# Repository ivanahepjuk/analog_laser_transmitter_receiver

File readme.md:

Laser transmitter and receiver, version 2.0

!!! Please consider, that using the laser beam is dangerus and wearing protective tools is required !!!

This schematics and PCB was designed and created by me and I am ok with using this resources for your own educational purposes.
If you decide to build it and use it in public, you can use my credentials as a resource, of course,)

Created August 2016 ivanahepjuk@gmail.com

DATA:

There are project folders created by PCB tool Kicad 4.0.4, but I dont think it will work once you download it and open in Kicad 
(because Kicad has terrible library management). Therefore I created another folder with pdf document with schematics, 
pcb boards and I also included the .svg file in case you want to manually tune the boards a bit using for example inscape.
Enjoy

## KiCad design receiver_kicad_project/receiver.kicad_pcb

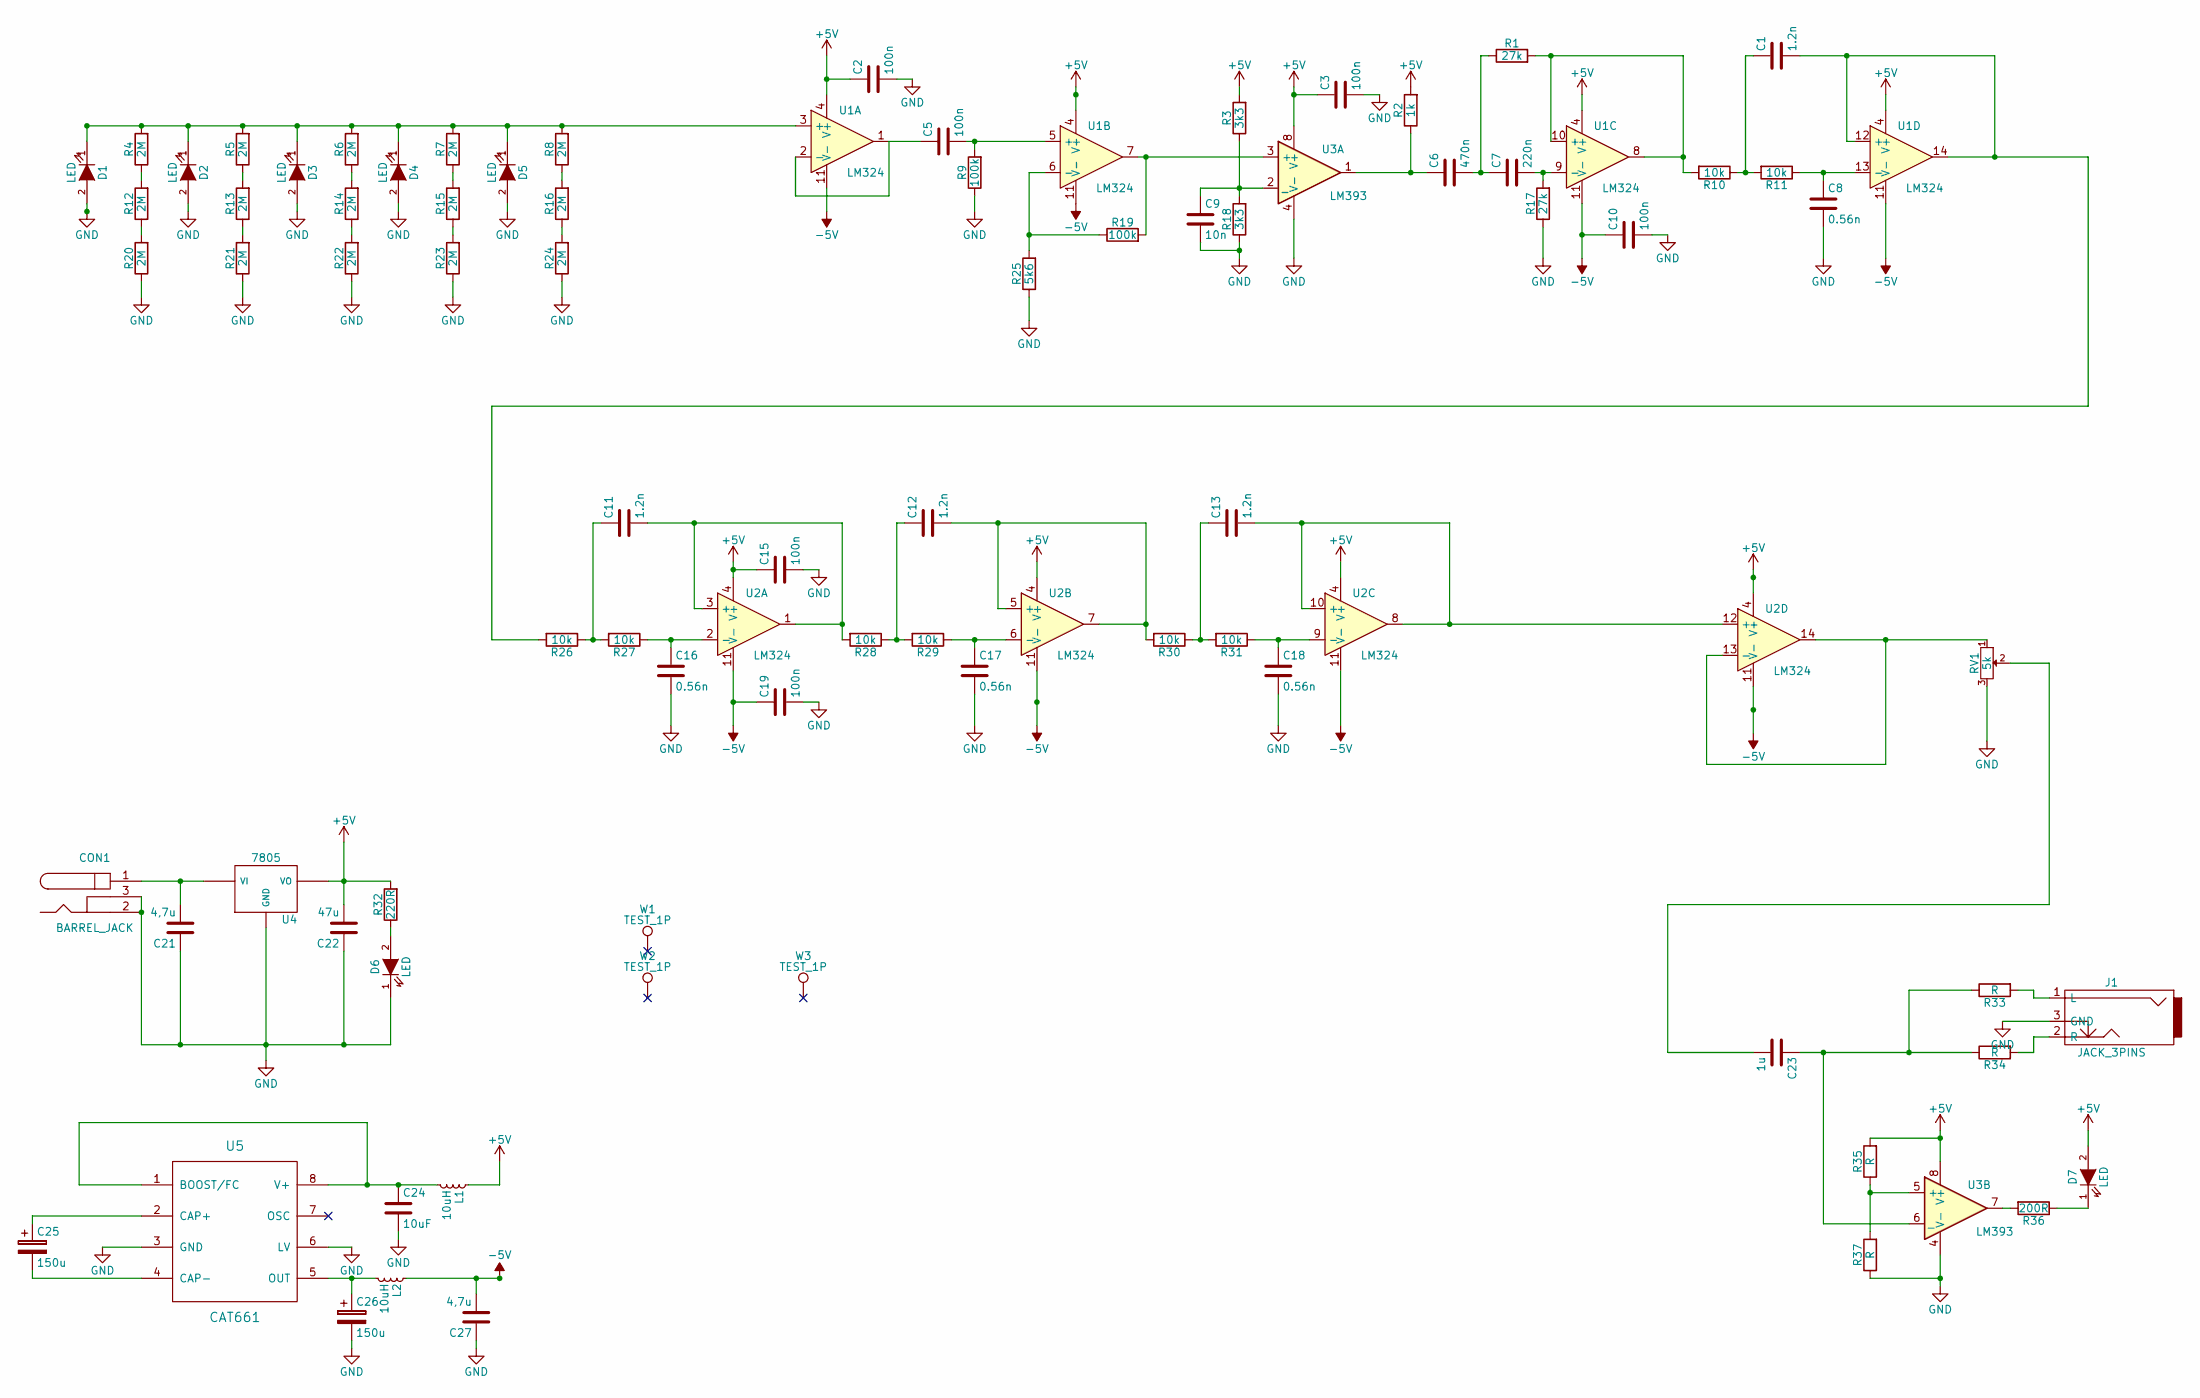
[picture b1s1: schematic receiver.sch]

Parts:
C1, C11, C12, C13: 1.2n; C_Disc_D3_P2.5
C2, C3, C5, C10, C15, C19: 100n; C_Disc_D3_P2.5
C6: 470n; C_Disc_D3_P2.5
C7: 220n; C_Disc_D3_P2.5
C8, C16, C17, C18: 0.56n; C_Disc_D3_P2.5
C9: 10n; C_Disc_D3_P2.5
C21: 4,7u; C_Radial_D5_L11_P2.5
C22: 47u; C_Radial_D5_L11_P2.5
C23: 1u; C_Radial_D5_L11_P2.5
C24: 10uF; C_Radial_D5_L11_P2.5
C25, C26: 150u; C_Radial_D10_L13_P5
C27: 4,7u; C_Radial_D5_L6_P2.5
CON1: BARREL_JACK; JACK_ALIM
D1, D2, D3, D4, D5, D6, D7: LED; LED-5MM
J1: JACK_3PINS; jack_3.5mm_3pins
L1, L2: 10uH; Choke_Toroid_horizontal_Diameter3-5mm_Amidon-T12
R1, R17: 27k; Resistor_Horizontal_RM7mm
R2: 1k; Resistor_Horizontal_RM7mm
R3, R18: 3k3; Resistor_Horizontal_RM7mm
R4, R5, R6, R7, R8, R12, R13, R14, R15, R16, R20, R21, R22, R23, R24: 2M; Resistor_Horizontal_RM7mm
R9, R19: 100k; Resistor_Horizontal_RM7mm
R10, R11, R26, R27, R28, R29, R30, R31: 10k; Resistor_Horizontal_RM7mm
R25: 5k6; Resistor_Horizontal_RM7mm
R32: 220R; Resistor_Horizontal_RM7mm
R33, R34, R35, R37: R; Resistor_Horizontal_RM7mm
R36: 200R; Resistor_Horizontal_RM7mm
RV1: 5k; Potentiometer_Bourns_3296W_3-8Zoll_Inline_ScrewUp
U1, U2: LM324; DIP-14_W7.62mm_LongPads
U3: LM393; PDIP-8
U4: 7805; TO-252-2Lead
U5: CAT661; PDIP-8
W1, W2, W3: TEST_1P; Pin_Header_Straight_1x01

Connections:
+5V: C2.1, C3.1, C15.1, C22.2, D7.2 (A), L1.1, R2.2, R3.2, R32.2, R35.2, U1.4 (V+), U2.4 (V+), U3.8 (V+), U4.3 (VO)
-5V: C10.1, C19.1, C27.2, L2.1, U1.11 (V-), U2.11 (V-)
GND: C2.2, C3.2, C8.2, C9.2, C10.2, C15.2, C16.2, C17.2, C18.2, C19.2, C21.1, C22.1, C24.2, C26.2, C27.1, CON1.2, CON1.3, D1.2 (A), D2.2 (A), D3.2 (A), D4.2 (A), D5.2 (A), D6.1 (K), J1.3 (GND), R9.1, R17.1, R18.1, R20.1, R21.1, R22.1, R23.1, R24.1, R25.1, R37.1, RV1.3, U3.4 (V-), U4.2 (GND), U5.3 (GND), U5.6 (LV)
unnamed: C1.1, R10.1, R11.2
unnamed: C1.2, R26.2, U1.12 (+), U1.14
unnamed: C5.1, U1.1, U1.2 (-)
unnamed: C5.2, R9.2, U1.5 (+)
unnamed: C6.1, R2.1, U3.1
unnamed: C6.2, C7.1, R1.1
unnamed: C7.2, R17.2, U1.9 (-)
unnamed: C8.1, R11.1, U1.13 (-)
unnamed: C9.1, R3.1, R18.2, U3.2 (_)
unnamed: C11.1, R26.1, R27.2
unnamed: C11.2, R28.2, U2.1, U2.3 (+)
unnamed: C12.1, R28.1, R29.2
unnamed: C12.2, R30.2, U2.5 (+), U2.7
unnamed: C13.1, R30.1, R31.2
unnamed: C13.2, U2.8, U2.10 (+), U2.12 (+)
unnamed: C16.1, R27.1, U2.2 (-)
unnamed: C17.1, R29.1, U2.6 (-)
unnamed: C18.1, R31.1, U2.9 (-)
unnamed: C21.2, CON1.1, U4.1 (VI)
unnamed: C23.1, R33.1, R34.1, U3.6 (_)
unnamed: C23.2, RV1.2
unnamed: C24.1, L1.2, U5.1 (BOOST/FC), U5.8 (V+)
unnamed: C25.1, U5.2 (CAP+)
unnamed: C25.2, U5.4 (CAP-)
unnamed: C26.1, L2.2, U5.5 (OUT)
unnamed: D1.1 (K), D2.1 (K), D3.1 (K), D4.1 (K), D5.1 (K), R4.2, R5.2, R6.2, R7.2, R8.2, U1.3 (+)
unnamed: D6.2 (A), R32.1
unnamed: D7.1 (K), R36.1
unnamed: J1.1 (L), R33.2
unnamed: J1.2 (R), R34.2
unnamed: R1.2, R10.2, U1.8, U1.10 (+)
unnamed: R12.1, R20.2
unnamed: R4.1, R12.2
unnamed: R13.1, R21.2
unnamed: R5.1, R13.2
unnamed: R14.1, R22.2
unnamed: R6.1, R14.2
unnamed: R15.1, R23.2
unnamed: R7.1, R15.2
unnamed: R16.1, R24.2
unnamed: R8.1, R16.2
unnamed: R19.1, R25.2, U1.6 (-)
unnamed: R19.2, U1.7, U3.3 (+)
unnamed: R35.1, R37.2, U3.5 (+)
unnamed: R36.2, U3.7
unnamed: RV1.1, U2.13 (-), U2.14

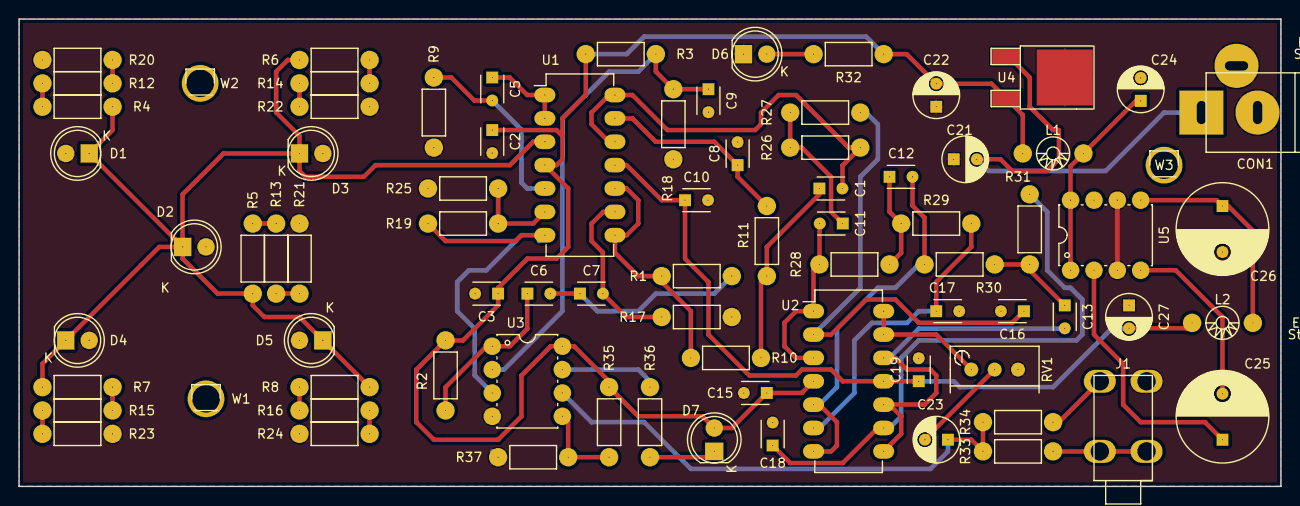
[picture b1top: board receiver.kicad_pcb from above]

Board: 2 copper layers, 137.2 x 50.8 mm, 81 parts (0 on the bottom side), 49 nets.

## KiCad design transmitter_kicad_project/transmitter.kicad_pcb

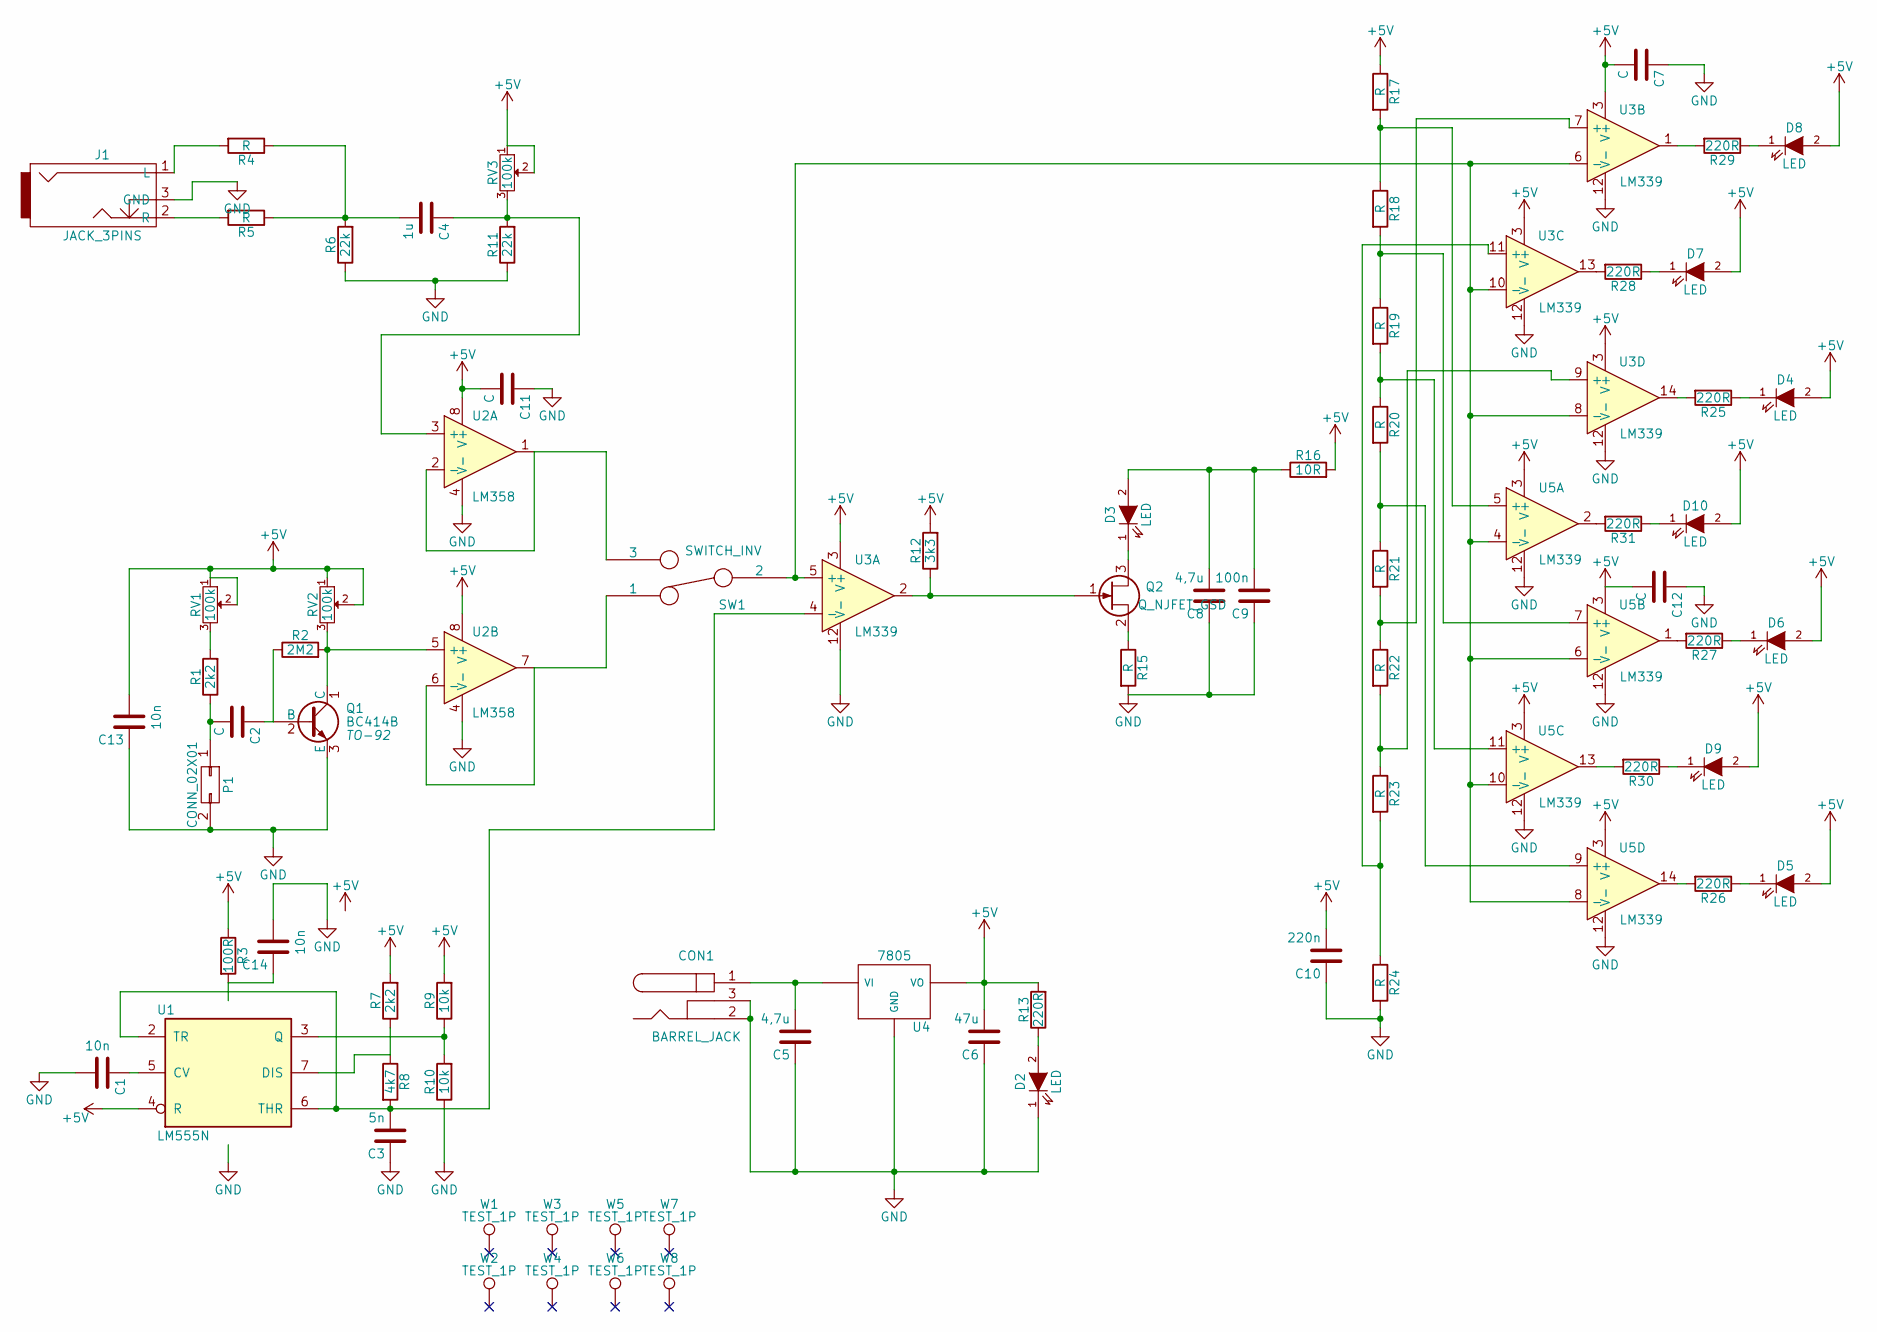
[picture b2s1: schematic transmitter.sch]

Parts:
C1, C13, C14: 10n; C_Disc_D3_P2.5
C2: C; C_Disc_D7.5_P5
C3: 5n; C_Disc_D3_P2.5
C4: 1u; C_Disc_D3_P2.5
C5, C8: 4,7u; C_Radial_D5_L11_P2
C6: 47u; C_Radial_D5_L11_P2
C7, C11, C12: C; C_Disc_D3_P2.5
C9: 100n; C_Disc_D3_P2.5
C10: 220n; C_Disc_D3_P2.5
CON1: BARREL_JACK
D2: LED; LED-3MM
D3, D4, D5, D6, D7, D8, D9, D10: LED; LED-5MM
J1: JACK_3PINS; jack_3.5mm_3pins
P1: CONN_02X01; C_Radial_D8_L11.5_P3.5
Q1: BC414B; TO-92
Q2: Q_NJFET_GSD; TO-220_Neutral123_Vertical_LargePads
R1, R7: 2k2; Resistor_Horizontal_RM7mm
R2: 2M2; Resistor_Horizontal_RM7mm
R3: 100R; Resistor_Horizontal_RM7mm
R4, R5, R15, R17, R18, R19, R20, R21, R22, R23, R24: R; Resistor_Horizontal_RM7mm
R6, R11: 22k; Resistor_Horizontal_RM7mm
R8: 4k7; Resistor_Horizontal_RM7mm
R9, R10: 10k; Resistor_Horizontal_RM7mm
R12: 3k3; Resistor_Horizontal_RM7mm
R13, R25, R26, R27, R28, R29, R30, R31: 220R; Resistor_Horizontal_RM7mm
R16: 10R; Resistor_Horizontal_RM7mm
RV1, RV2, RV3: 100k; Potentiometer_Trimmer-Suntan-TSR-3386C
SW1: SWITCH_INV; Pin_Header_Straight_1x03
U1: LM555N; PDIP-8
U2: LM358; PDIP-8
U3, U5: LM339; DIP-14_W7.62mm_LongPads
U4: 7805; TO-252-2Lead
W1, W2, W3, W4, W5, W6, W7, W8: TEST_1P; Pin_Header_Straight_1x01

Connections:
+5V: C6.2, C7.2, C10.2, C11.2, C12.2, C13.2, D4.2 (A), D5.2 (A), D6.2 (A), D7.2 (A), D8.2 (A), D9.2 (A), D10.2 (A), R3.1, R7.2, R9.2, R12.2, R13.2, R16.2, R17.1, RV1.1, RV1.2, RV2.1, RV2.2, RV3.1, RV3.2, U1.4 (R), U2.8 (V+), U3.3 (V+), U4.3 (VO), U5.3 (V+)
GND: C1.2, C3.1, C5.1, C6.1, C7.1, C8.1, C9.1, C10.1, C11.1, C12.1, C13.1, C14.2, CON1.2, CON1.3, D2.1 (K), J1.3 (GND), P1.2, Q1.3 (E), R6.1, R10.1, R11.1, R15.2, R24.2, U1.1 (GND), U2.4 (V-), U3.12 (V-), U4.2 (GND), U5.12 (V-)
unnamed: C1.1, U1.5 (CV)
unnamed: C2.1, Q1.2 (B), R2.1
unnamed: C2.2, P1.1, R1.1
unnamed: C3.2, R8.2, U1.2 (TR), U1.6 (THR), U3.4 (-)
unnamed: C4.1, R11.2, RV3.3, U2.3 (+)
unnamed: C4.2, R4.1, R5.1, R6.2
unnamed: C5.2, CON1.1, U4.1 (VI)
unnamed: C8.2, C9.2, D3.2 (A), R16.1
unnamed: D2.2 (A), R13.1
unnamed: D4.1 (K), R25.1
unnamed: D5.1 (K), R26.1
unnamed: D6.1 (K), R27.1
unnamed: D7.1 (K), R28.1
unnamed: D8.1 (K), R29.1
unnamed: D9.1 (K), R30.1
unnamed: D10.1 (K), R31.1
unnamed: J1.1 (L), R4.2
unnamed: J1.2 (R), R5.2
unnamed: Q1.1 (C), R2.2, RV2.3, U2.5 (+)
unnamed: Q2.1 (G), R12.1, U3.2
unnamed: R1.2, RV1.3
unnamed: R7.1, R8.1, U1.7 (DIS)
unnamed: R9.1, R10.2, U1.3 (Q)
unnamed: R17.2, R18.1, U5.5 (+)
unnamed: R18.2, R19.1, U5.7 (+)
unnamed: R19.2, R20.1, U5.11 (+)
unnamed: R20.2, R21.1, U5.9 (+)
unnamed: R21.2, R22.1, U3.7 (+)
unnamed: R22.2, R23.1, U3.9 (+)
unnamed: R23.2, R24.1, U3.11 (+)
unnamed: R25.2, U3.14
unnamed: R26.2, U5.14
unnamed: R27.2, U5.1
unnamed: R28.2, U3.13
unnamed: R29.2, U3.1
unnamed: R30.2, U5.13
unnamed: R31.2, U5.2
unnamed: SW1.1, U2.6 (-), U2.7
unnamed: SW1.2, U3.5 (+), U3.6 (-), U3.8 (-), U3.10 (-), U5.4 (-), U5.6 (-), U5.8 (-), U5.10 (-)
unnamed: SW1.3, U2.1, U2.2 (-)
VCC: C14.1, R3.2, U1.8 (VCC)

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
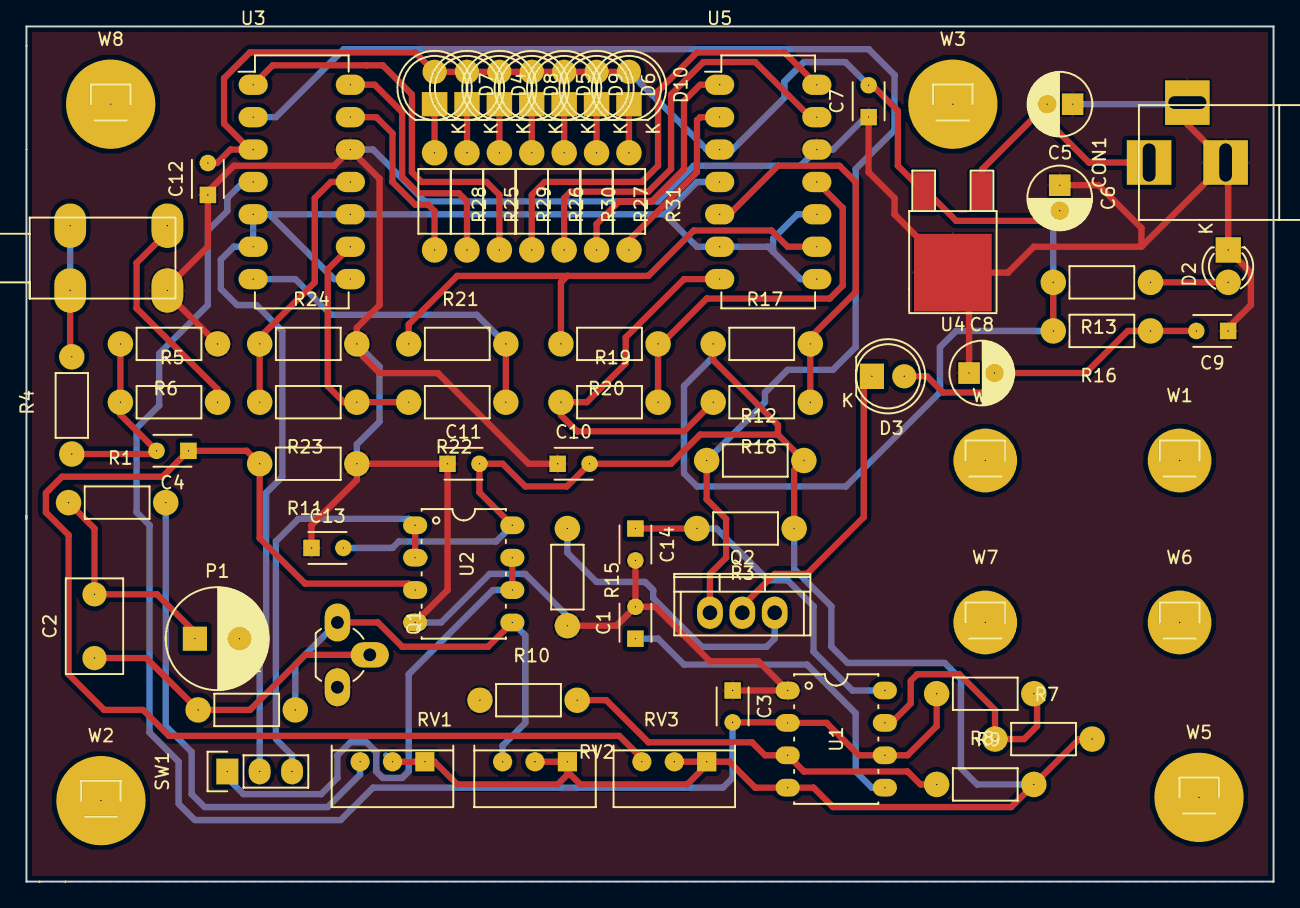
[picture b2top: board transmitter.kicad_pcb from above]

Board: 2 copper layers, 97.8 x 67.1 mm, 75 parts (0 on the bottom side), 45 nets.
